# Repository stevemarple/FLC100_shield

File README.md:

FLC100_shield
=============

Shield for FLC100 fluxgate magnetometer

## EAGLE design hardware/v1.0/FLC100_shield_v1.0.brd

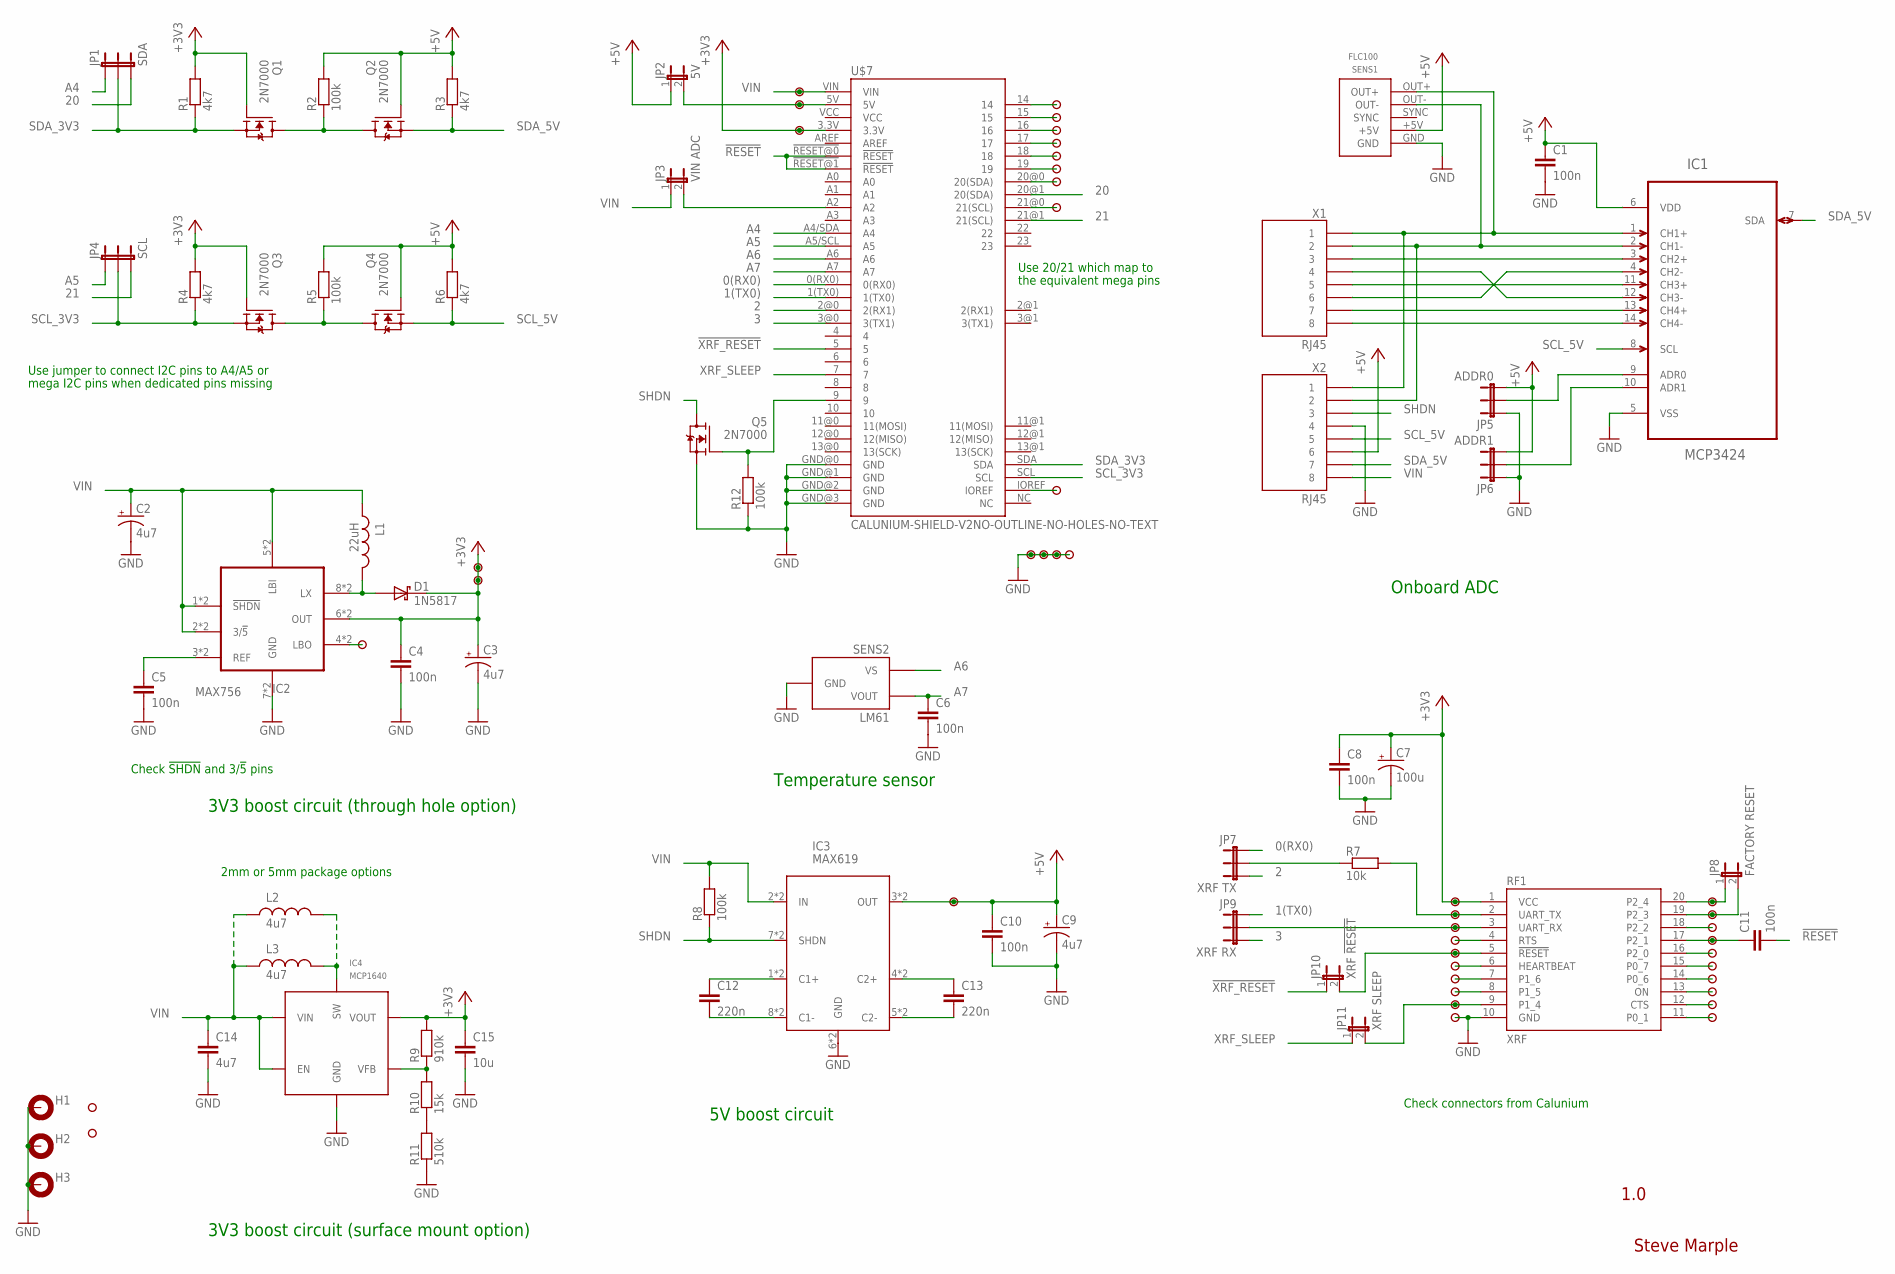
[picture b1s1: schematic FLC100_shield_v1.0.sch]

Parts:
C1, C4, C5, C6, C8, C10, C11: 100n; CAP-PTH-SMALL
C2, C3, C9: 4u7; CPOL-RADIAL-10UF-25V
C7: 100u; CPOL-RADIAL-10UF-25V
C12, C13: 220n; CAP-PTH-5MM
C14: 4u7; 1206-HAND
C15: 10u; 1206-HAND
D1: 1N5817; DIODE-TH-0.4
H1, H2, H3: MOUNT-PAD-ROUND3.0; 3,0-PAD
IC1: MCP3424; SOIC127P600X175-14N
IC2: MAX756; DIL08-SOIC8
IC3: MAX619; DIL08-SOIC8
IC4: MCP1640; SOT23-6
JP1: SDA; 1X03
JP2: 5V; 1X02
JP3: VIN ADC; 1X02
JP4: SCL; 1X03
JP5: ADDR0; 1X03
JP6: ADDR1; 1X03
JP7: XRF TX; 1X03
JP8: FACTORY RESET; 1X02
JP9: XRF RX; 1X03
JP10: XRF !RESET; 1X02
JP11: XRF SLEEP; 1X02
L1: 22uH; INDUCTOR-TH-5MM
L2: 4u7; INDUCTOR-TH-2MM
L3: 4u7; INDUCTOR-TH-5MM
Q1, Q2, Q3, Q4, Q5: 2N7000; TO-92
R1, R3, R4, R6: 4k7; RES-AXIAL-0.4
R2, R5, R8, R12: 100k; RES-AXIAL-0.4
R7: 10k; RES-AXIAL-0.4
R9: 910k; 1206-HAND
R10: 15k; 1206-HAND
R11: 510k; 1206-HAND
RF1: XRF; XBEE
SENS1: FLC100
SENS2: LM61; TO-92
U$1, U$2, U$3, U$4, U$5, U$6, U$8, U$9, U$10, U$11, U$12, U$13, U$14, U$15, U$16, U$17, U$18, U$19, U$20, U$21, U$22, U$23, U$24, U$25, U$26, U$27, U$28, U$29, U$30, U$31, U$32, U$33, U$34, U$35, U$36, U$37, U$38, U$39, U$40, U$41, U$42, U$43: PAD
U$7: CALUNIUM-SHIELD-V2NO-OUTLINE-NO-HOLES-NO-TEXT; CALUNIUM-SHIELD-NO-OUTLINE-NO-HOLES-NO-TEXT-V2
X1, X2: RJ45; RJ45-8

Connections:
0(RX0): JP7.1, U$7.0(RX0)
1(TX0): JP9.1, U$7.1(TX0)
2: JP7.3, U$7.2@0 (2(RX1))
3: JP9.3, U$7.3@0 (3(TX1))
20: JP1.3, U$7.20@1 (20(SDA))
21: JP4.3, U$7.21@1 (21(SCL))
!RESET: C11.2, U$7.!RESET@0 (!RESET), U$7.!RESET@1 (!RESET)
!XRF_RESET: JP10.1, U$7.5
+3V3: C3.1 (+), C4.1, C7.1 (+), C8.1, C15.1, D1.C, IC2.6 (OUT), IC2.6@1 (OUT), IC4.5 (VOUT), Q1.2 (G), Q3.2 (G), R1.P$2 (2), R4.P$2 (2), R9.2, RF1.1 (VCC), U$7.3.3V, U$9.1, U$36.1, U$42.1, U$43.1
+5V: C1.1, C9.1 (+), C10.1, IC1.6 (VDD), IC3.3 (OUT), IC3.3@1 (OUT), JP2.1, JP5.3, JP6.3, Q2.2 (G), Q4.2 (G), R2.P$2 (2), R3.P$2 (2), R5.P$2 (2), R6.P$2 (2), SENS1.+5V, U$41.1, X2.6
A4: JP1.1, U$7.A4/SDA (A4)
A5: JP4.1, U$7.A5/SCL (A5)
A6: SENS2.1 (VS), U$7.A6
A7: C6.1, SENS2.2 (VOUT), U$7.A7
CHECK1: IC1.9 (ADR0), JP5.2
CHECK2: IC1.10 (ADR1), JP6.2
GND: C1.2, C2.2 (-), C3.2 (-), C4.2, C5.2, C6.2, C7.2 (-), C8.2, C9.2 (-), C10.2, C14.2, C15.2, H1.B3,0, H2.B3,0, H3.B3,0, IC1.5 (VSS), IC2.7 (GND), IC2.7@1 (GND), IC3.6 (GND), IC3.6@1 (GND), IC4.2 (GND), JP5.1, JP6.1, Q5.1 (S), R11.1, R12.P$1 (1), RF1.10 (GND), SENS1.GND, SENS2.3 (GND), U$7.GND@0 (GND), U$7.GND@1 (GND), U$7.GND@2 (GND), U$7.GND@3 (GND), U$27.1, U$37.1, U$38.1, U$39.1, U$40.1, X2.4
unnamed: Q1.3 (D), Q2.3 (D), R2.P$1 (1)
unnamed: Q3.3 (D), Q4.3 (D), R5.P$1 (1)
unnamed: C12.2, IC3.8 (C1-), IC3.8@1 (C1-)
unnamed: C12.1, IC3.1 (C1+), IC3.1@1 (C1+)
unnamed: C13.1, IC3.4 (C2+), IC3.4@1 (C2+)
unnamed: C13.2, IC3.5 (C2-), IC3.5@1 (C2-)
unnamed: JP8.1, RF1.20 (P2_4), U$10.1
unnamed: JP8.2, RF1.19 (P2_3), U$12.1
unnamed: R7.P$2 (2), RF1.2 (UART_TX), U$11.1
unnamed: JP9.2, RF1.3 (UART_RX), U$13.1
unnamed: RF1.4 (RTS), U$15.1
unnamed: JP10.2, RF1.5 (!RESET), U$17.1
unnamed: RF1.6 (HEARTBEAT), U$19.1
unnamed: RF1.7 (P1_6), U$21.1
unnamed: RF1.8 (P1_5), U$23.1
unnamed: JP11.2, RF1.9 (P1_4), U$25.1
unnamed: RF1.18 (P2_2), U$14.1
unnamed: C11.1, RF1.17 (P2_1), U$16.1
unnamed: RF1.16 (P2_0), U$18.1
unnamed: RF1.15 (P0_7), U$20.1
unnamed: RF1.14 (P0_6), U$22.1
unnamed: RF1.13 (ON), U$24.1
unnamed: RF1.12 (CTS), U$26.1
unnamed: RF1.11 (P0_1), U$28.1
unnamed: IC2.4 (LBO), IC2.4@1 (LBO), U$8.1
unnamed: Q5.2 (G), R12.P$2 (2), U$7.9
unnamed: JP3.2, U$7.A2
unnamed: JP7.2, R7.P$1 (1)
unnamed: JP2.2, U$7.5V, U$35.1
unnamed: D1.A, IC2.8 (LX), IC2.8@1 (LX), L1.P$2 (2)
unnamed: C5.1, IC2.3 (REF), IC2.3@1 (REF)
unnamed: IC1.1 (CH1+), SENS1.OUT+, X1.1, X2.1
unnamed: IC1.2 (CH1-), SENS1.OUT-, X1.2, X2.2
unnamed: IC1.3 (CH2+), X1.3
unnamed: IC1.4 (CH2-), X1.6
unnamed: IC1.11 (CH3+), X1.5
unnamed: IC1.12 (CH3-), X1.4
unnamed: IC1.13 (CH4+), X1.7
unnamed: IC1.14 (CH4-), X1.8
unnamed: U$7.21@0 (21(SCL)), U$32.1
unnamed: IC4.1 (SW), L2.P$2 (2), L3.P$2 (2)
unnamed: R10.1, R11.2
unnamed: U$1.1, U$7.14
unnamed: U$2.1, U$7.15
unnamed: U$3.1, U$7.16
unnamed: IC4.4 (VFB), R9.1, R10.2
unnamed: U$4.1, U$7.17
unnamed: U$5.1, U$7.18
unnamed: U$6.1, U$7.19
unnamed: U$7.20@0 (20(SDA)), U$31.1
unnamed: U$7.IOREF, U$33.1
SCL_3V3: JP4.2, Q3.1 (S), R4.P$1 (1), U$7.SCL
SCL_5V: IC1.8 (SCL), Q4.1 (S), R6.P$1 (1), X2.5
SDA_3V3: JP1.2, Q1.1 (S), R1.P$1 (1), U$7.SDA
SDA_5V: IC1.7 (SDA), Q2.1 (S), R3.P$1 (1), X2.7
SHDN: IC3.7 (SHDN), IC3.7@1 (SHDN), Q5.3 (D), R8.P$1 (1), X2.3
VIN: C2.1 (+), C14.1, IC2.1 (!SHDN), IC2.1@1 (!SHDN), IC2.2 (3/!5), IC2.2@1 (3/!5), IC2.5 (LBI), IC2.5@1 (LBI), IC3.2 (IN), IC3.2@1 (IN), IC4.3 (EN), IC4.6 (VIN), JP3.1, L1.P$1 (1), L2.P$1 (1), L3.P$1 (1), R8.P$2 (2), U$7.VIN, U$34.1, X2.8
XRF_SLEEP: JP11.1, U$7.7

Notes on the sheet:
1.0
Steve Marple
Check connectors from Calunium
Use jumper to connect I2C pins to A4/A5 or
Check !SHDN! and 3/!5! pins
3V3 boost circuit (through hole option)
Use 20/21 which map to
the equivalent mega pins
2mm or 5mm package options
mega I2C pins when dedicated pins missing
3V3 boost circuit (surface mount option)
Onboard ADC
5V boost circuit
Temperature sensor

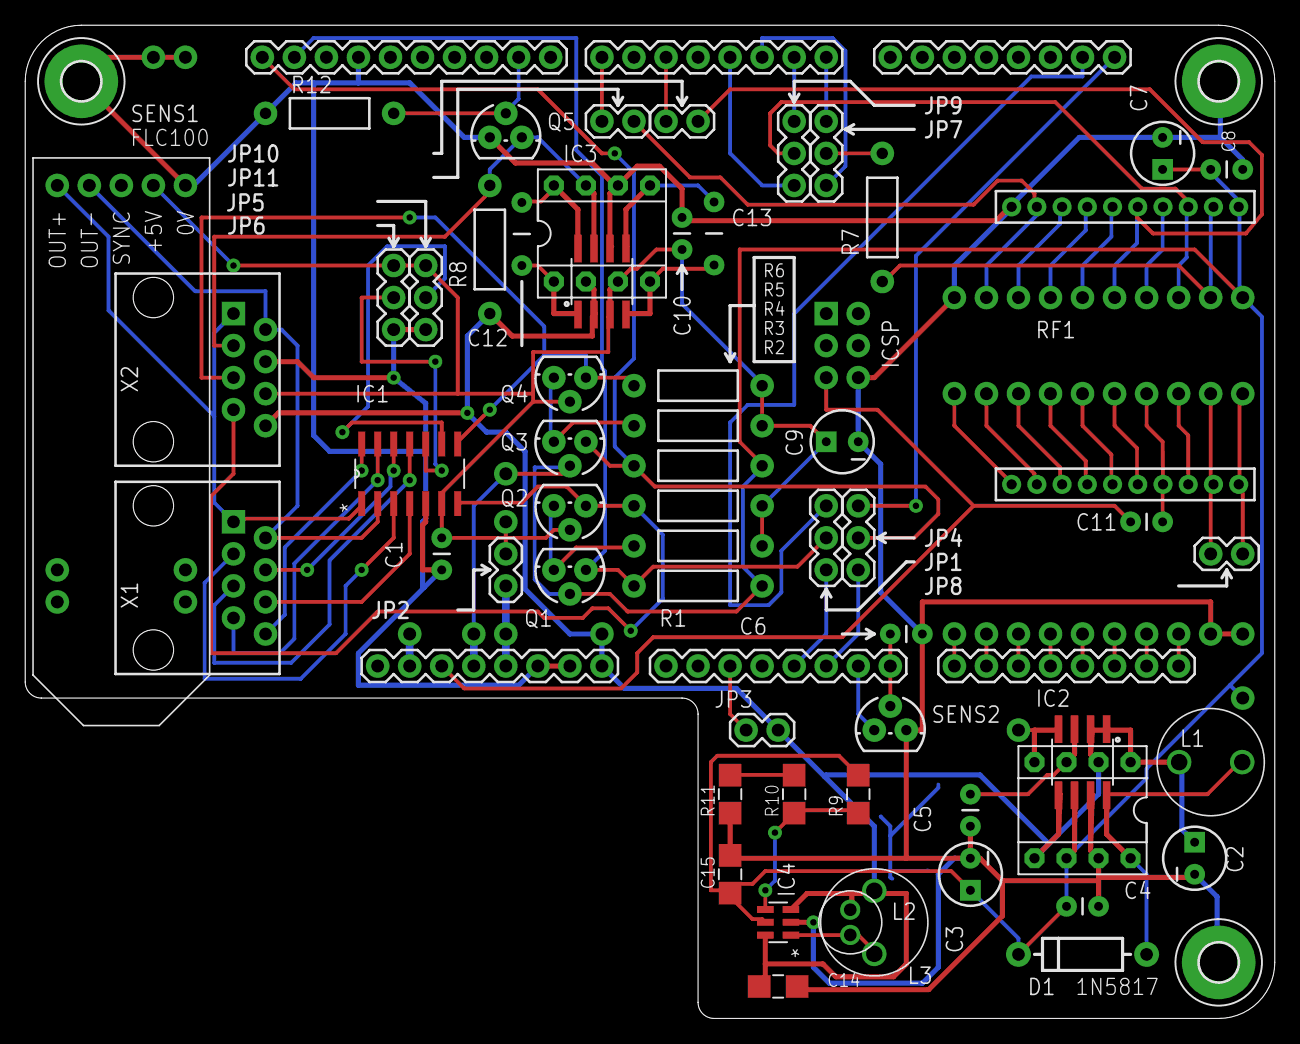
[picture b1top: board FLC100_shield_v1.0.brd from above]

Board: 2 copper layers, 99.1 x 78.7 mm, 102 parts (0 on the bottom side), 75 nets.

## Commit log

2012-08-21 Adding v1.0 schematic and board design.
2012-09-07 Adding files used for first production run.
2013-12-13 Adding software to test shield.

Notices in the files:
parts and their libraries:
SparkFun: Licensing: CC v3.0 Share-Alike You are welcome to use this library for commercial purposes.
